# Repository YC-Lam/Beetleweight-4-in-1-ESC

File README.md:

# beetleweight 4 in 1 brushless ESC
 a 4 in 1 ESC designed for UK beetleweight robots. It can power two brushless drive and one weapon motor.

## Features
- Two 20A brushless drive motor
- Single 80A brushless weapon motor
- Integrated fuse to accommodate BBB rules
- On-board gyroscope to invert controls when bot is inverted (optional)
- On-board BLE reciever to control bot over an XBox controller
- Supports 2-6s Lipo battery
- configurable UVLO, OVP and OCP
- Compact with a 50x50mm dimension
- Single side SMD soldering for easy manufaturing (some hand soldered resistors at the back)

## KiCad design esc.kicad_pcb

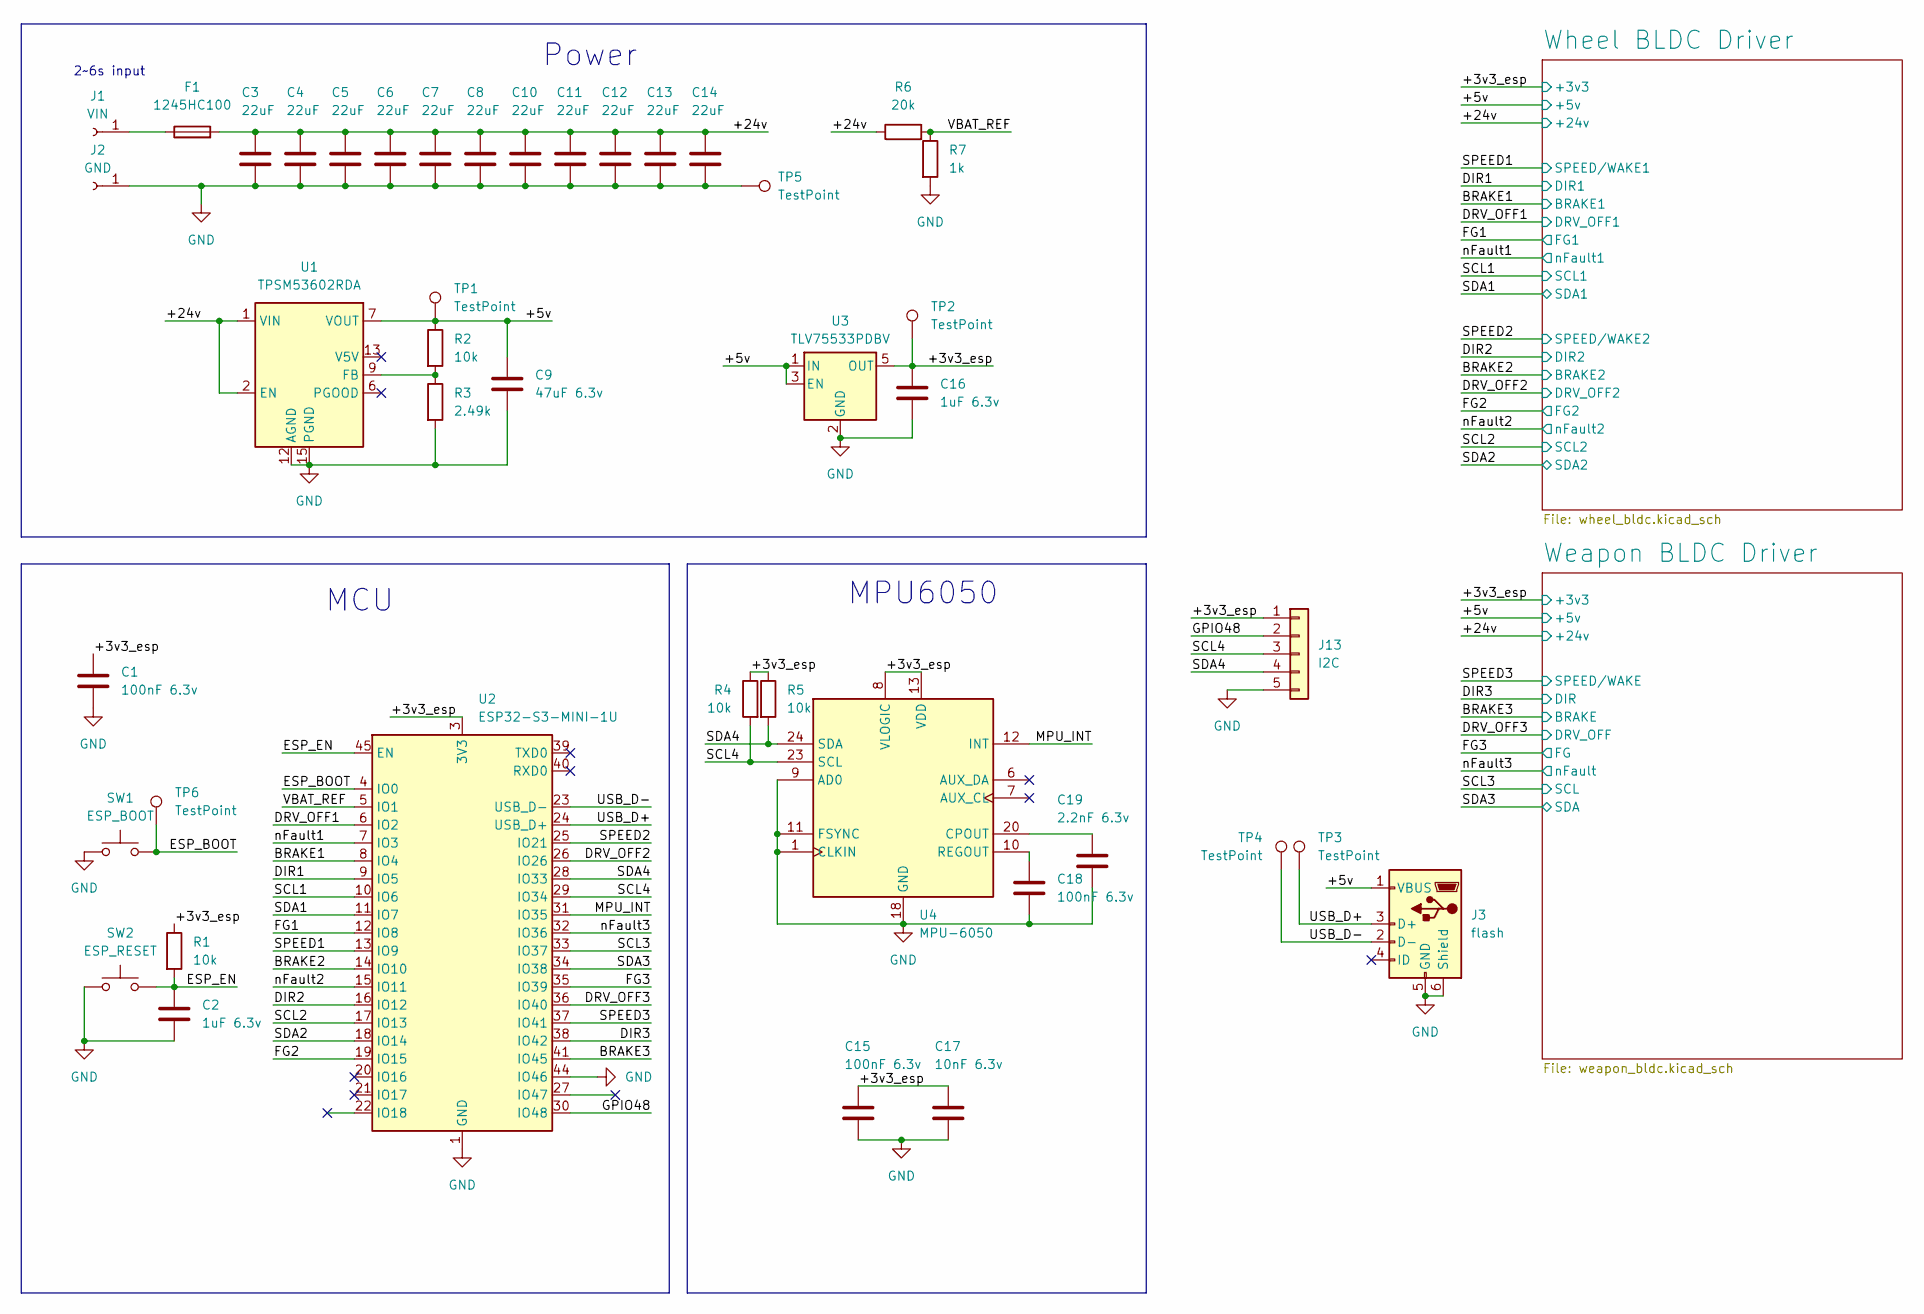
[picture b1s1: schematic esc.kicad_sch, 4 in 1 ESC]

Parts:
C1, C15, C18: 100nF 6.3v; C_0402_1005Metric
C2: 1uF 6.3v; C_0603_1608Metric_Pad1.08x0.95mm_HandSolder
C3, C4, C5, C6, C7, C8, C10, C11, C12, C13, C14: 22uF; C_0805_2012Metric
C9: 47uF 6.3v; C_0603_1608Metric
C16: 1uF 6.3v; C_0402_1005Metric
C17: 10nF 6.3v; C_0402_1005Metric
C19: 2.2nF 6.3v; C_0402_1005Metric
F1: 1245HC100; 1245HC
J1: VIN; WIRE
J2: GND; WIRE
J3: flash; USB_Micro-B_Molex_47346-0001
J13: I2C; signal wire
R1: 10k; R_0603_1608Metric_Pad0.98x0.95mm_HandSolder
R2, R4, R5: 10k; R_0402_1005Metric
R3: 2.49k; R_0402_1005Metric
R6: 20k; R_0402_1005Metric
R7: 1k; R_0402_1005Metric
SW1: ESP_BOOT; SW_SPST_B3U-1000P
SW2: ESP_RESET; SW_SPST_B3U-1000P
TP1, TP2, TP3, TP4, TP5, TP6: TestPoint; TestPoint_Pad_D1.0mm
U1: TPSM53602RDA; Texas_B3QFN-14-1EP_5x5.5mm_P0.65mm
U2: ESP32-S3-MINI-1U; ESP32-S2-MINI-1U
U3: TLV75533PDBV; SOT-23-5
U4: MPU-6050; InvenSense_QFN-24_4x4mm_P0.5mm

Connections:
/+3v3_esp: C1.1, C15.1, C16.1, C17.1, J13.1, R1.1, R4.1, R5.1, TP2.1, U2.3 (3V3), U3.5 (OUT), U4.8 (VLOGIC), U4.13 (VDD); also elsewhere on the board
/+5v: C9.1, J3.1 (VBUS), R2.1, TP1.1, U1.7 (VOUT), U1.8 (VOUT), U3.1 (IN), U3.3 (EN); also elsewhere on the board
/+24v: C3.1, C4.1, C5.1, C6.1, C7.1, C8.1, C10.1, C11.1, C12.1, C13.1, C14.1, F1.2, R6.1, U1.1 (VIN), U1.2 (EN), U1.14 (VIN); also elsewhere on the board
/BRAKE1: U2.8 (IO4); also elsewhere on the board
/BRAKE2: U2.14 (IO10); also elsewhere on the board
/BRAKE3: U2.41 (IO45); also elsewhere on the board
/DIR1: U2.9 (IO5); also elsewhere on the board
/DIR2: U2.16 (IO12); also elsewhere on the board
/DIR3: U2.38 (IO42); also elsewhere on the board
/DRV_OFF1: U2.6 (IO2); also elsewhere on the board
/DRV_OFF2: U2.26 (IO26); also elsewhere on the board
/DRV_OFF3: U2.36 (IO40); also elsewhere on the board
/ESP_BOOT: SW1.2, TP6.1, U2.4 (IO0)
/ESP_EN: C2.1, R1.2, SW2.2, U2.45 (EN)
/FG1: U2.12 (IO8); also elsewhere on the board
/FG2: U2.19 (IO15); also elsewhere on the board
/FG3: U2.35 (IO39); also elsewhere on the board
/GPIO48: J13.2, U2.30 (IO48)
/MPU_INT: U2.31 (IO35), U4.12 (INT)
/SCL1: U2.10 (IO6); also elsewhere on the board
/SCL2: U2.17 (IO13); also elsewhere on the board
/SCL3: U2.33 (IO37); also elsewhere on the board
/SCL4: J13.3, R4.2, U2.29 (IO34), U4.23 (SCL)
/SDA1: U2.11 (IO7); also elsewhere on the board
/SDA2: U2.18 (IO14); also elsewhere on the board
/SDA3: U2.34 (IO38); also elsewhere on the board
/SDA4: J13.4, R5.2, U2.28 (IO33), U4.24 (SDA)
/SPEED1: U2.13 (IO9); also elsewhere on the board
/SPEED2: U2.25 (IO21); also elsewhere on the board
/SPEED3: U2.37 (IO41); also elsewhere on the board
/USB_D+: J3.3 (D+), TP3.1, U2.24 (USB_D+)
/USB_D-: J3.2 (D-), TP4.1, U2.23 (USB_D-)
/VBAT_REF: R6.2, R7.1, U2.5 (IO1)
/nFault1: U2.7 (IO3); also elsewhere on the board
/nFault2: U2.15 (IO11); also elsewhere on the board
/nFault3: U2.32 (IO36); also elsewhere on the board
GND: C1.2, C2.2, C3.2, C4.2, C5.2, C6.2, C7.2, C8.2, C9.2, C10.2, C11.2, C12.2, C13.2, C14.2, C15.2, C16.2, C17.2, C18.2, C19.2, J2.1, J3.5 (GND), J3.6 (Shield), J13.5, R3.2, R7.2, SW1.1, SW2.1, TP5.1, U1.3 (PGND), U1.10 (PGND), U1.11 (PGND), U1.12 (AGND), U1.15 (PGND), U2.1 (GND), U2.2 (GND), U2.42 (GND), U2.43 (GND), U2.44 (IO46), U2.46 (GND), U2.47 (GND), U2.48 (GND), U2.49 (GND), U2.50 (GND), U2.51 (GND), U2.52 (GND), U2.53 (GND), U2.54 (GND), U2.55 (GND), U2.56 (GND), U2.57 (GND), U2.58 (GND), U2.59 (GND), U2.60 (GND), U2.61 (GND), U2.62 (GND), U2.63 (GND), U2.64 (GND), U2.65 (GND), U3.2 (GND), U4.1 (CLKIN), U4.9 (AD0), U4.11 (FSYNC), U4.18 (GND); also elsewhere on the board
unnamed: F1.1, J1.1
unnamed: R2.2, R3.1, U1.9 (FB)
unnamed: C19.1, U4.20 (CPOUT)
unnamed: C18.1, U4.10 (REGOUT)

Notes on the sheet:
MPU6050
Power
2~6s input
MCU

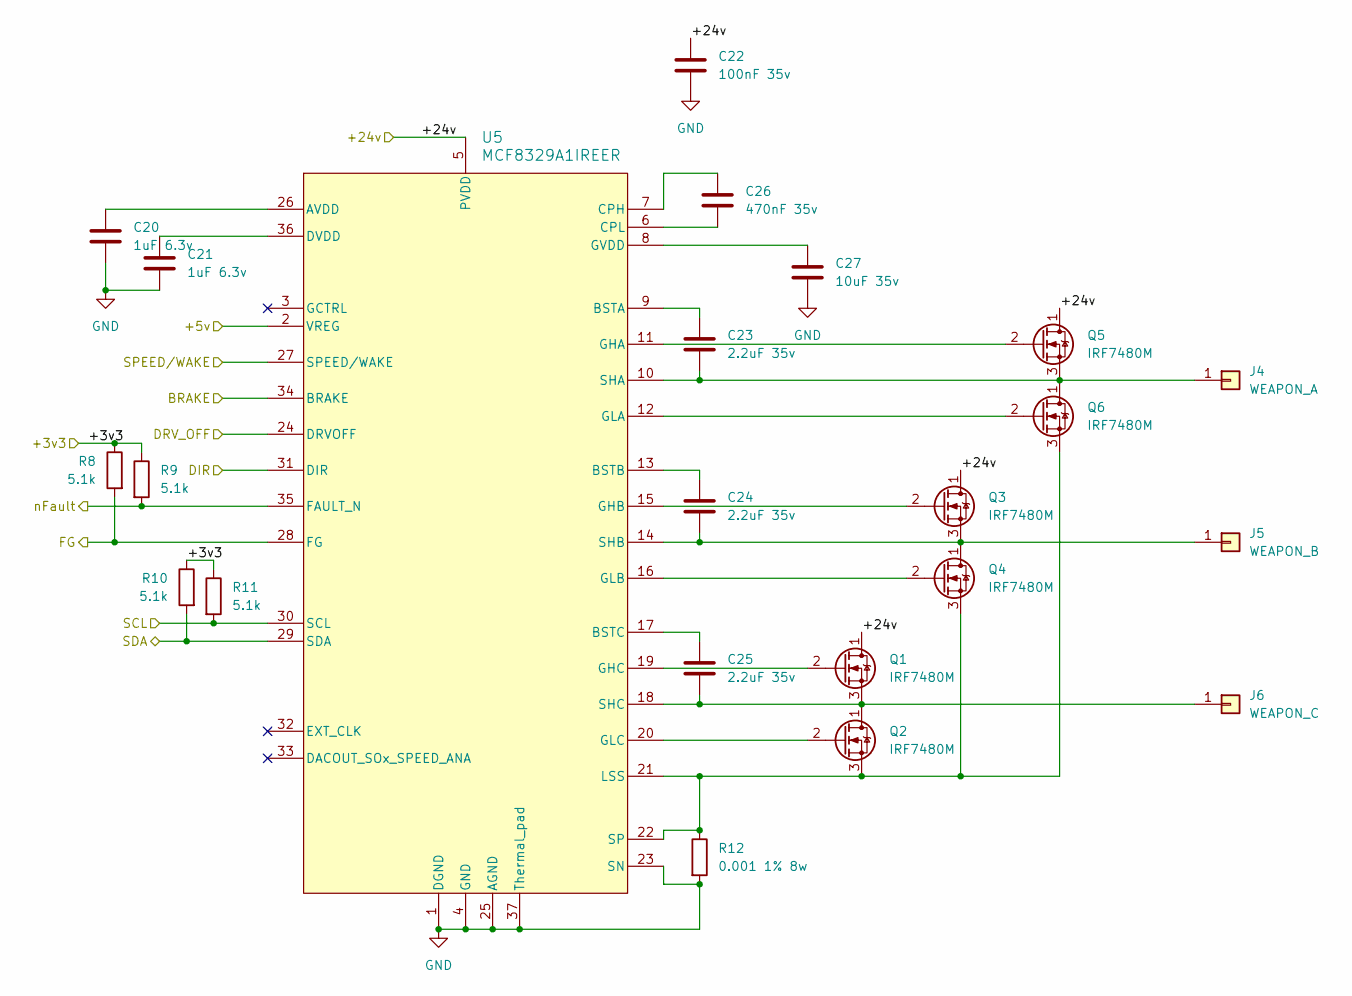
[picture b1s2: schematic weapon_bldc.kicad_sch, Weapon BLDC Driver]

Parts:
C20, C21: 1uF 6.3v; C_0402_1005Metric
C22: 100nF 35v; C_0402_1005Metric
C23, C24, C25: 2.2uF 35v; C_0402_1005Metric
C26: 470nF 35v; C_0402_1005Metric
C27: 10uF 35v; C_0603_1608Metric
J4: WEAPON_A; WIRE
J5: WEAPON_B; WIRE
J6: WEAPON_C; WIRE
Q1, Q2, Q3, Q4, Q5, Q6: IRF7480M; DirectFET_ME
R8, R9, R10, R11: 5.1k; R_0402_1005Metric
R12: 0.001 1% 8w; R_2512_6332Metric
U5: MCF8329A1IREER; REE0036A-IPC_A

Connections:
/+3v3_esp: R8.1, R9.1, R10.1, R11.1; also elsewhere on the board
/+5v: U5.2 (VREG); also elsewhere on the board
/+24v: C22.1, Q1.1 (D), Q3.1 (D), Q5.1 (D), U5.5 (PVDD); also elsewhere on the board
/BRAKE3: U5.34 (BRAKE); also elsewhere on the board
/DIR3: U5.31 (DIR); also elsewhere on the board
/DRV_OFF3: U5.24 (DRVOFF); also elsewhere on the board
/FG3: R8.2, U5.28 (FG); also elsewhere on the board
/SCL3: R11.2, U5.30 (SCL); also elsewhere on the board
/SDA3: R10.2, U5.29 (SDA); also elsewhere on the board
/SPEED3: U5.27 (SPEED/WAKE); also elsewhere on the board
/nFault3: R9.2, U5.35 (FAULT_N); also elsewhere on the board
GND: C20.2, C21.2, C22.2, C27.2, R12.2, U5.1 (DGND), U5.4 (GND), U5.23 (SN), U5.25 (AGND), U5.37 (Thermal_pad); also elsewhere on the board
unnamed: C23.2, J4.1, Q5.3 (S), Q6.1 (D), U5.10 (SHA)
unnamed: C24.2, J5.1, Q3.3 (S), Q4.1 (D), U5.14 (SHB)
unnamed: C25.2, J6.1, Q1.3 (S), Q2.1 (D), U5.18 (SHC)
unnamed: Q1.2 (G), U5.19 (GHC)
unnamed: Q2.2 (G), U5.20 (GLC)
unnamed: Q2.3 (S), Q4.3 (S), Q6.3 (S), R12.1, U5.21 (LSS), U5.22 (SP)
unnamed: Q3.2 (G), U5.15 (GHB)
unnamed: Q4.2 (G), U5.16 (GLB)
unnamed: Q5.2 (G), U5.11 (GHA)
unnamed: Q6.2 (G), U5.12 (GLA)
unnamed: C20.1, U5.26 (AVDD)
unnamed: C23.1, U5.9 (BSTA)
unnamed: C24.1, U5.13 (BSTB)
unnamed: C25.1, U5.17 (BSTC)
unnamed: C26.1, U5.7 (CPH)
unnamed: C26.2, U5.6 (CPL)
unnamed: C21.1, U5.36 (DVDD)
unnamed: C27.1, U5.8 (GVDD)

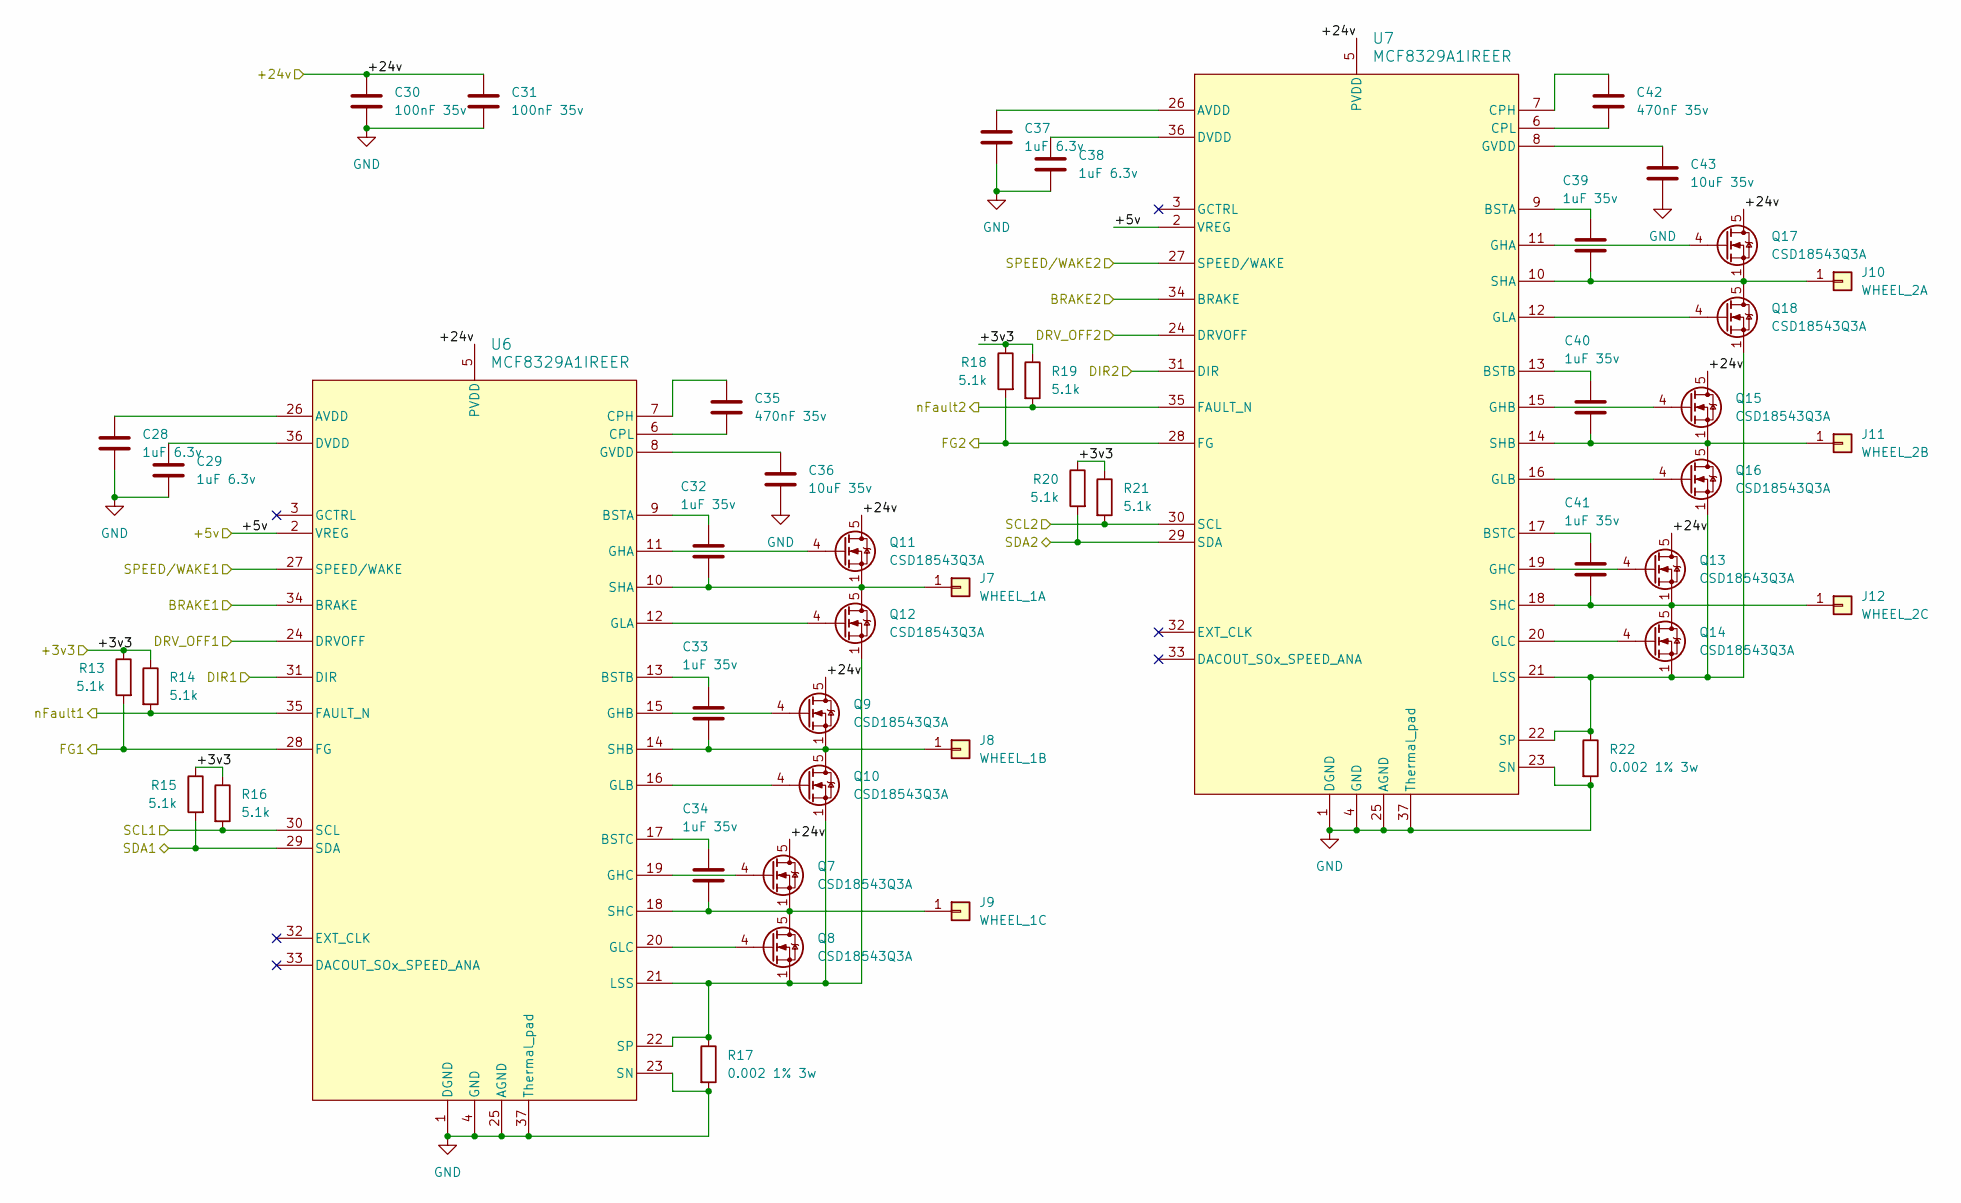
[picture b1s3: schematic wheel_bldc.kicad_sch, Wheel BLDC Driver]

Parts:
C28, C29, C37, C38: 1uF 6.3v; C_0402_1005Metric
C30, C31: 100nF 35v; C_0402_1005Metric
C32, C33, C34, C39, C40, C41: 1uF 35v; C_0402_1005Metric
C35, C42: 470nF 35v; C_0402_1005Metric
C36, C43: 10uF 35v; C_0603_1608Metric
J7: WHEEL_1A; WIRE
J8: WHEEL_1B; WIRE
J9: WHEEL_1C; WIRE
J10: WHEEL_2A; WIRE
J11: WHEEL_2B; WIRE
J12: WHEEL_2C; WIRE
Q7, Q8, Q9, Q10, Q11, Q12, Q13, Q14, Q15, Q16, Q17, Q18: CSD18543Q3A; VSON-8_3.3x3.3mm_P0.65mm_NexFET
R13, R14, R15, R16, R18, R19, R20, R21: 5.1k; R_0402_1005Metric
R17, R22: 0.002 1% 3w; R_2512_6332Metric
U6, U7: MCF8329A1IREER; REE0036A-IPC_A

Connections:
/+3v3_esp: R13.1, R14.1, R15.1, R16.1, R18.1, R19.1, R20.1, R21.1; also elsewhere on the board
/+5v: U6.2 (VREG), U7.2 (VREG); also elsewhere on the board
/+24v: C30.1, C31.1, Q7.5 (D), Q9.5 (D), Q11.5 (D), Q13.5 (D), Q15.5 (D), Q17.5 (D), U6.5 (PVDD), U7.5 (PVDD); also elsewhere on the board
/BRAKE1: U6.34 (BRAKE); also elsewhere on the board
/BRAKE2: U7.34 (BRAKE); also elsewhere on the board
/DIR1: U6.31 (DIR); also elsewhere on the board
/DIR2: U7.31 (DIR); also elsewhere on the board
/DRV_OFF1: U6.24 (DRVOFF); also elsewhere on the board
/DRV_OFF2: U7.24 (DRVOFF); also elsewhere on the board
/FG1: R13.2, U6.28 (FG); also elsewhere on the board
/FG2: R18.2, U7.28 (FG); also elsewhere on the board
/SCL1: R16.2, U6.30 (SCL); also elsewhere on the board
/SCL2: R21.2, U7.30 (SCL); also elsewhere on the board
/SDA1: R15.2, U6.29 (SDA); also elsewhere on the board
/SDA2: R20.2, U7.29 (SDA); also elsewhere on the board
/SPEED1: U6.27 (SPEED/WAKE); also elsewhere on the board
/SPEED2: U7.27 (SPEED/WAKE); also elsewhere on the board
/nFault1: R14.2, U6.35 (FAULT_N); also elsewhere on the board
/nFault2: R19.2, U7.35 (FAULT_N); also elsewhere on the board
GND: C28.2, C29.2, C30.2, C31.2, C36.2, C37.2, C38.2, C43.2, R17.2, R22.2, U6.1 (DGND), U6.4 (GND), U6.23 (SN), U6.25 (AGND), U6.37 (Thermal_pad), U7.1 (DGND), U7.4 (GND), U7.23 (SN), U7.25 (AGND), U7.37 (Thermal_pad); also elsewhere on the board
unnamed: C32.2, J7.1, Q11.1 (S), Q11.2 (S), Q11.3 (S), Q12.5 (D), U6.10 (SHA)
unnamed: C33.2, J8.1, Q9.1 (S), Q9.2 (S), Q9.3 (S), Q10.5 (D), U6.14 (SHB)
unnamed: C34.2, J9.1, Q7.1 (S), Q7.2 (S), Q7.3 (S), Q8.5 (D), U6.18 (SHC)
unnamed: C39.2, J10.1, Q17.1 (S), Q17.2 (S), Q17.3 (S), Q18.5 (D), U7.10 (SHA)
unnamed: C40.2, J11.1, Q15.1 (S), Q15.2 (S), Q15.3 (S), Q16.5 (D), U7.14 (SHB)
unnamed: C41.2, J12.1, Q13.1 (S), Q13.2 (S), Q13.3 (S), Q14.5 (D), U7.18 (SHC)
unnamed: Q7.4 (G), U6.19 (GHC)
unnamed: Q8.4 (G), U6.20 (GLC)
unnamed: Q9.4 (G), U6.15 (GHB)
unnamed: Q10.4 (G), U6.16 (GLB)
unnamed: Q11.4 (G), U6.11 (GHA)
unnamed: Q12.4 (G), U6.12 (GLA)
unnamed: Q13.4 (G), U7.19 (GHC)
unnamed: Q14.4 (G), U7.20 (GLC)
unnamed: Q15.4 (G), U7.15 (GHB)
unnamed: Q16.4 (G), U7.16 (GLB)
unnamed: Q17.4 (G), U7.11 (GHA)
unnamed: Q18.4 (G), U7.12 (GLA)
unnamed: C28.1, U6.26 (AVDD)
unnamed: C32.1, U6.9 (BSTA)
unnamed: C33.1, U6.13 (BSTB)
unnamed: C34.1, U6.17 (BSTC)
unnamed: C35.1, U6.7 (CPH)
unnamed: C35.2, U6.6 (CPL)
unnamed: C29.1, U6.36 (DVDD)
unnamed: C36.1, U6.8 (GVDD)
unnamed: Q8.1 (S), Q8.2 (S), Q8.3 (S), Q10.1 (S), Q10.2 (S), Q10.3 (S), Q12.1 (S), Q12.2 (S), Q12.3 (S), R17.1, U6.21 (LSS), U6.22 (SP)
unnamed: C37.1, U7.26 (AVDD)
unnamed: C39.1, U7.9 (BSTA)
unnamed: C40.1, U7.13 (BSTB)
unnamed: C41.1, U7.17 (BSTC)
unnamed: C42.1, U7.7 (CPH)
unnamed: C42.2, U7.6 (CPL)
unnamed: C38.1, U7.36 (DVDD)
unnamed: C43.1, U7.8 (GVDD)
unnamed: Q14.1 (S), Q14.2 (S), Q14.3 (S), Q16.1 (S), Q16.2 (S), Q16.3 (S), Q18.1 (S), Q18.2 (S), Q18.3 (S), R22.1, U7.21 (LSS), U7.22 (SP)

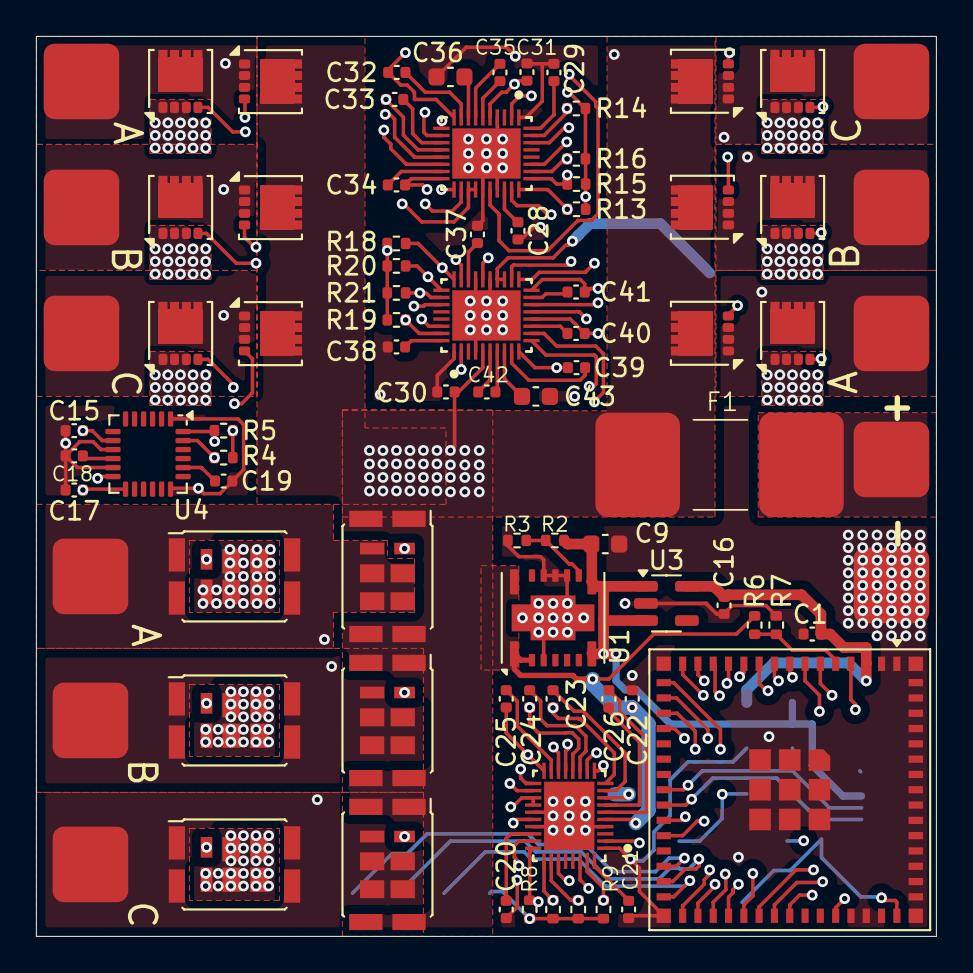
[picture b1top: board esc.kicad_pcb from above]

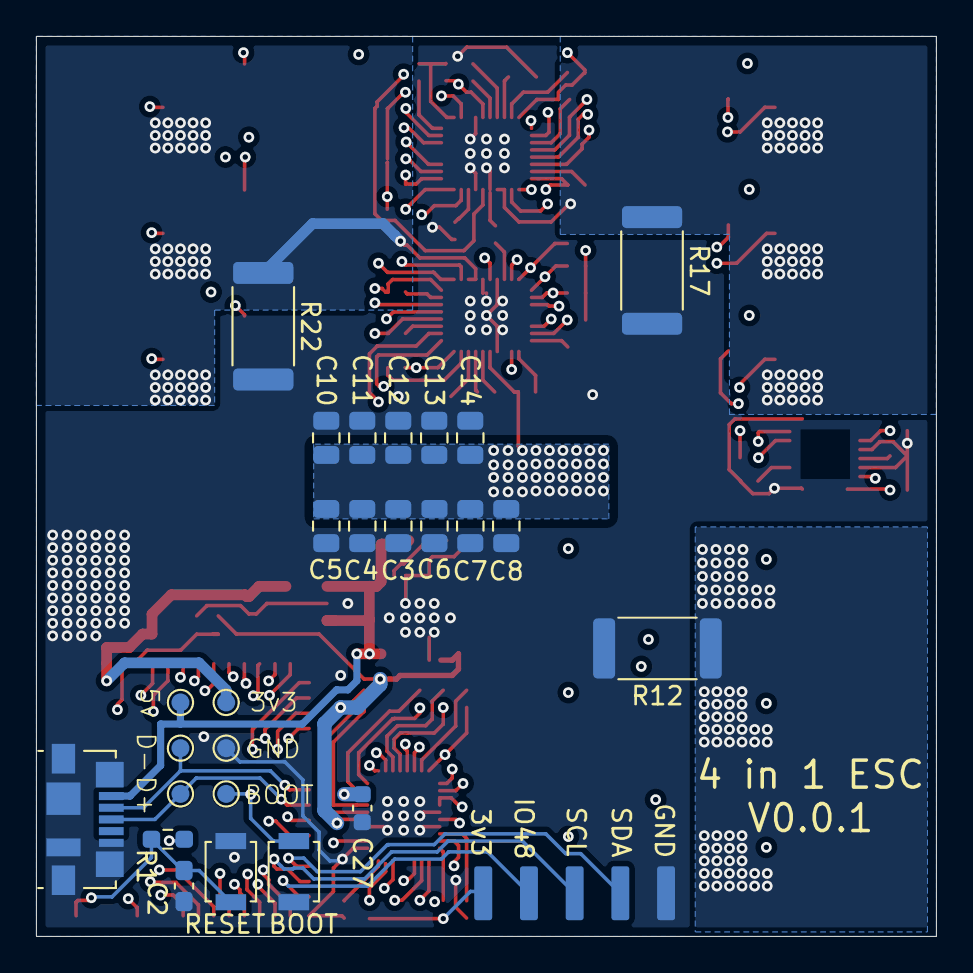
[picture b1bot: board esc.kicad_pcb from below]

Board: 4 copper layers, 50.0 x 50.0 mm, 112 parts (27 on the bottom side), 95 nets.

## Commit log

2025-11-15 main
